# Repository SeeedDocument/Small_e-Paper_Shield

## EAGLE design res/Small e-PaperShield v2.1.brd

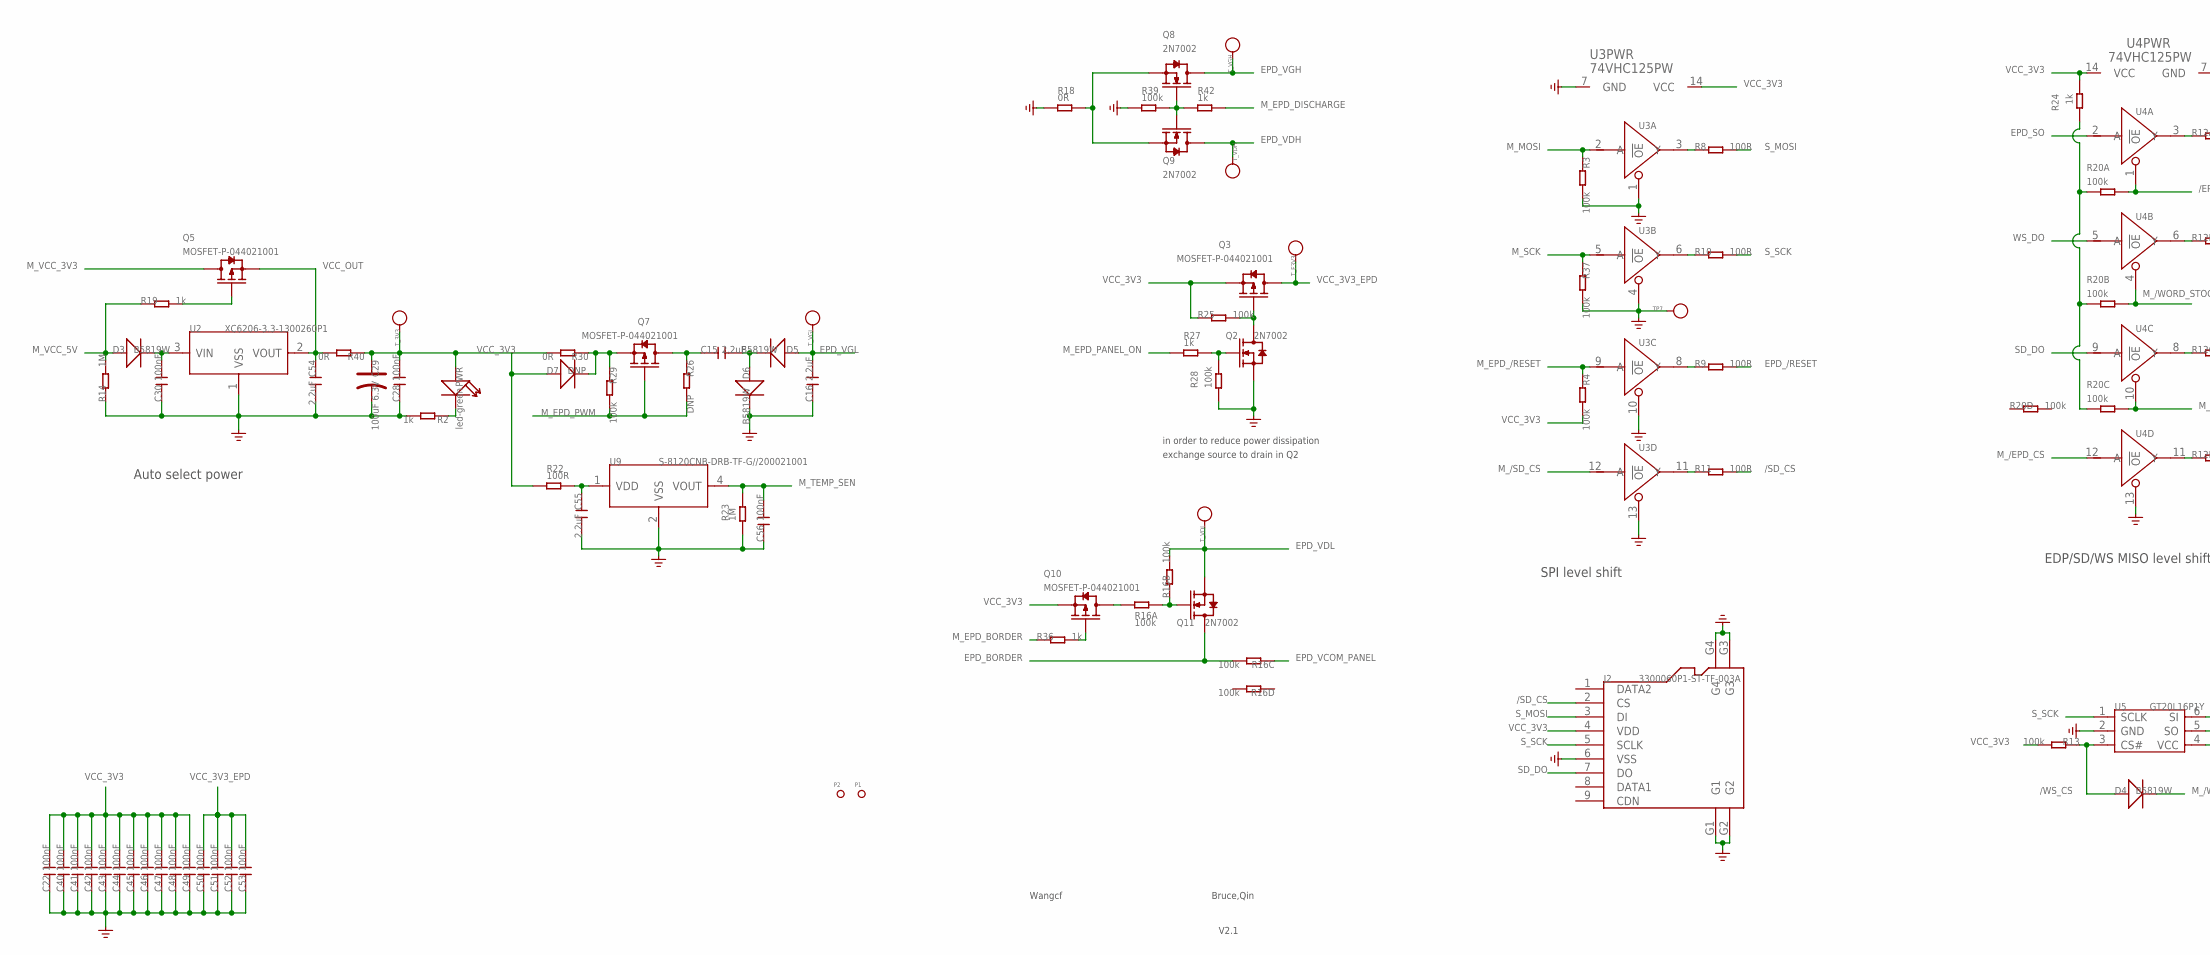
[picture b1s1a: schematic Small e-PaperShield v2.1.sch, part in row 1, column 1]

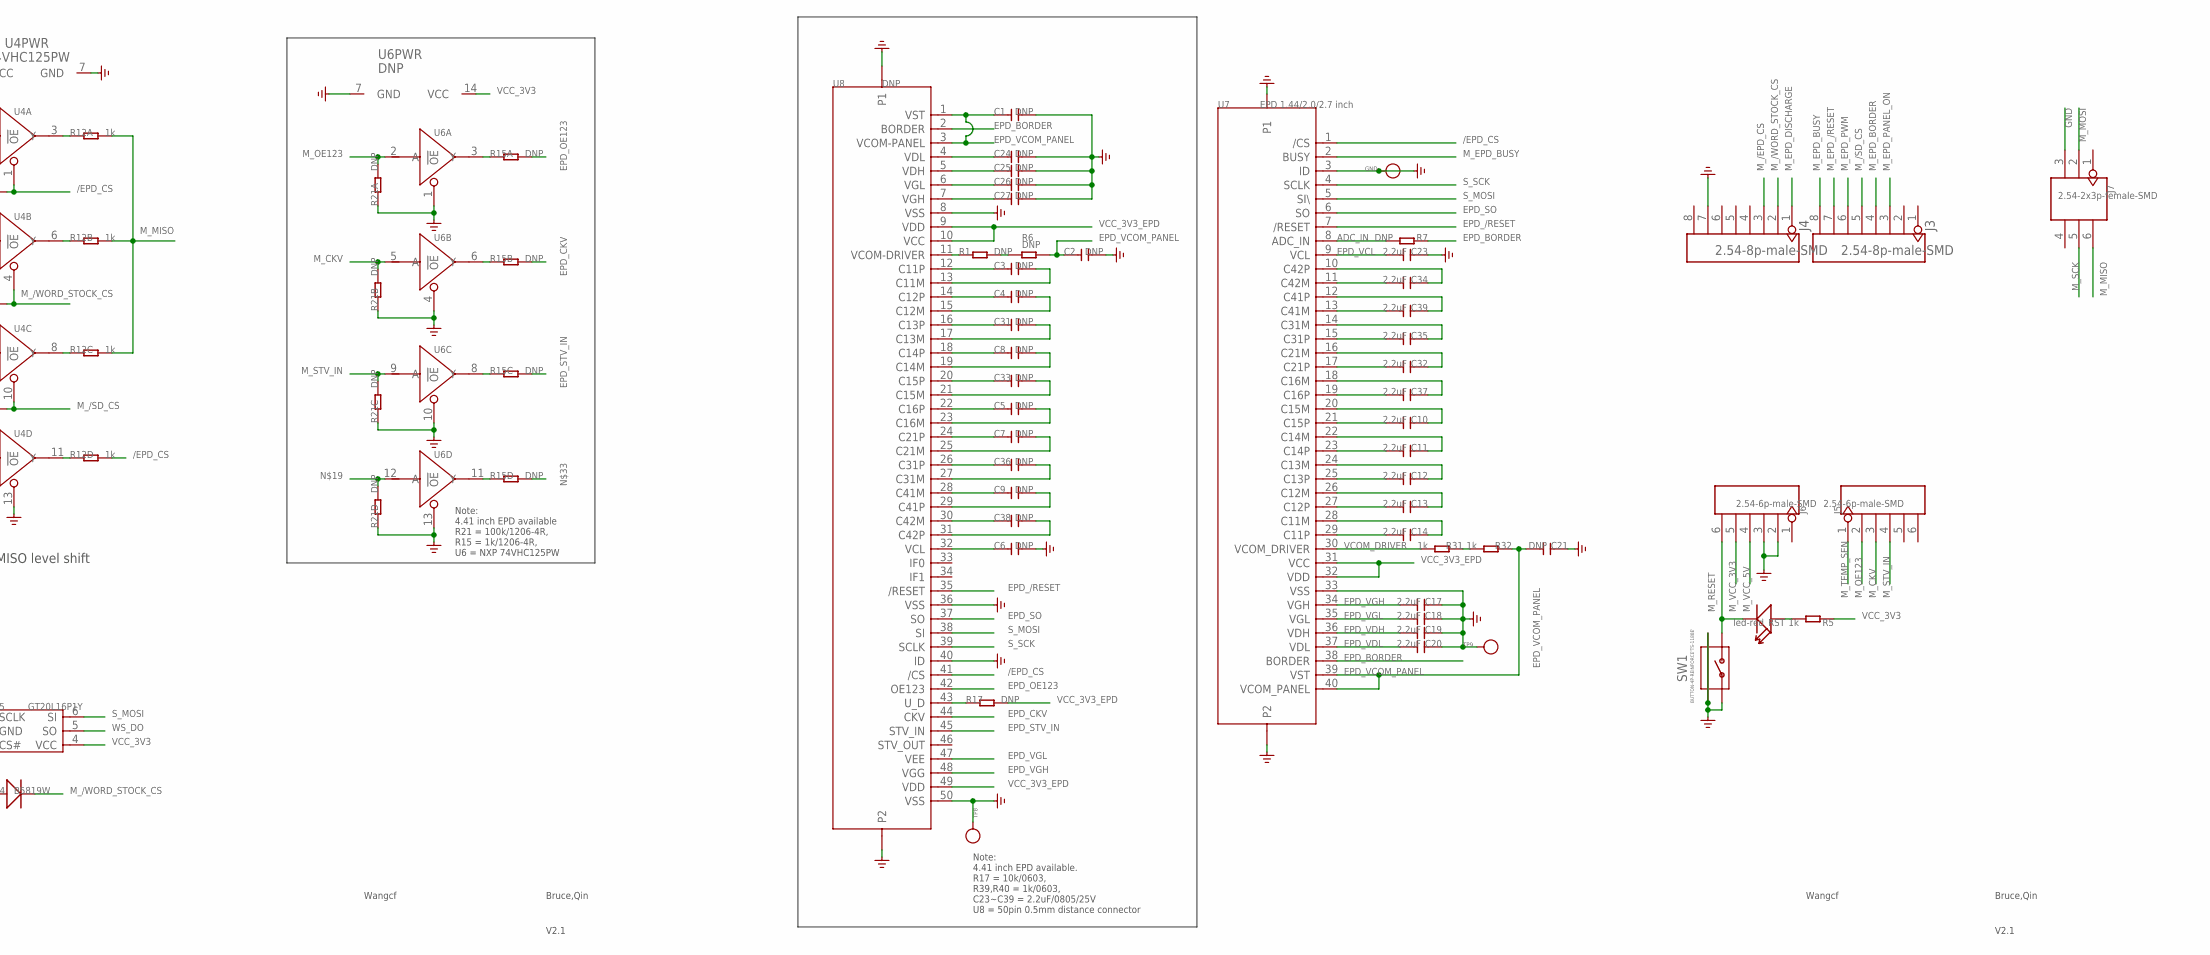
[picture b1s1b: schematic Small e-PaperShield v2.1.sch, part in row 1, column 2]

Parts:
C1, C2, C3, C4, C5, C6, C7, C8, C9, C21, C24, C25, C26, C27, C31, C33, C36, C38: DNP; C0805
C10, C11, C12, C13, C14, C15, C16, C17, C18, C19, C20, C23, C32, C34, C35, C37, C39, C54, C55: 2.2uF; C0805
C22, C28, C30, C40, C41, C42, C43, C44, C45, C46, C47, C48, C49, C50, C51, C52, C53, C56: 100nF; C0603
C29: 100uF 6.3V; AVX-B
D3, D4, D5, D6: B5819W; SOD123
D7: DNP; SOD123
GND: PAD-TEST-POINT'3535'; TP_3535
J2: 3300060P1-ST-TF-003A; 9P-SMD-W/-RING
J3, J4: 2.54-8p-male-SMD; 8P-2.54-SMD
J5, J6: 2.54-6p-male-SMD; 6P-2.54-SMD
J7: 2.54-2x3p-female-SMD; 2X3P-2.54-SMD
P1, P2: PAD-MARK; ROUND-MARK-1.0
PWR: led-green; LED-SIDE-VIEW-0603-RIGHT
Q2, Q8, Q9, Q11: 2N7002; SOT23
Q3, Q5, Q7, Q10: MOSFET-P-044021001; SOT23
R1, R6, R7, R17, R26: DNP; R0603
R2, R5, R19, R24, R27, R31, R32, R36, R42: 1k; R0603
R3, R4, R13, R25, R28, R29, R37, R39: 100k; R0603
R8, R9, R10, R11, R22: 100R; R0603
R12: 1k; 1206-8-3.3X2.4
R14, R23: 1M; R0603
R15, R21: DNP; 1206-8-3.3X2.4
R16, R20: 100k; 1206-8-3.3X2.4
R18, R30, R40: 0R; R0603
RST: led-red; LED-SIDE-VIEW-0603-RIGHT
SW1: BUTTON-4P-REINFORCE'TS-1188E'; 4P-SMD-7X3.5X3.5H
TP7, TP8, TP9: PAD-TEST-POINT'3535'; TP_3535
T_3V3: PAD-TEST-POINT'3535'; TP_3535
T_E3V3: PAD-TEST-POINT'3535'; TP_3535
T_VDH: PAD-TEST-POINT'3535'; TP_3535
T_VDL: PAD-TEST-POINT'3535'; TP_3535
T_VGH: PAD-TEST-POINT'3535'; TP_3535
T_VGL: PAD-TEST-POINT'3535'; TP_3535
U2: XC6206-3.3-1300260P1; SOT23
U3, U4: 74VHC125PW; TSSOP14
U5: GT20L16P1Y; SOT23-6
U6: DNP; TSSOP14
U7: EPD 1.44/2.0/2.7 inch; 40P-0.5
U8: DNP; 50P-0.5
U9: S-8120CNB-DRB-TF-G//200021001; SC-82AB

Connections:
3V3_LOG: R20.1, R20.2 (1), R20.3 (1), R24.2
/EPD_CS: R12.5 (2), R20.8 (2), U4.1 (!OE), U7.1 (/CS), U8.41 (/CS)
/SD_CS: J2.2 (CS), R11.2
/WS_CS: D4.+, R13.1, U5.3 (CS#)
ADC_IN: R7.2, U7.8 (ADC_IN)
EPD_/RESET: R9.2, U7.7 (/RESET), U8.35 (/RESET)
EPD_BORDER: Q11.3 (D), R7.1, R16.6 (2), U7.38 (BORDER), U8.2 (BORDER)
EPD_CKV: R15.7 (2), U8.44 (CKV)
EPD_OE123: R15.8 (2), U8.42 (OE123)
EPD_SO: U4.2 (A), U7.6 (SO), U8.37 (SO)
EPD_STV_IN: R15.6 (2), U8.45 (STV_IN)
EPD_VCL: C23.2, U7.9 (VCL)
EPD_VCOM_PANEL: C1.1, C2.1, C21.2, R6.2, R16.3 (1), R32.1, U7.39 (VST), U7.40 (VCOM_PANEL), U8.1 (VST), U8.3 (VCOM-PANEL)
EPD_VDH: C19.2, C25.1, Q9.3 (D), T_VDH.T, U7.36 (VDH), U8.5 (VDH)
EPD_VDL: C20.2, C24.1, Q11.2 (S), R16.7 (2), T_VDL.T, U7.37 (VDL), U8.4 (VDL)
EPD_VGH: C17.2, C27.1, Q8.3 (D), T_VGH.T, U7.34 (VGH), U8.7 (VGH), U8.48 (VGG)
EPD_VGL: C16.2, C18.2, C26.1, D5.+, T_VGL.T, U7.35 (VGL), U8.6 (VGL), U8.47 (VEE)
GND: C1.2, C2.2, C6.2, C16.1, C17.1, C18.1, C19.1, C20.1, C21.1, C22.1, C23.1, C24.2, C25.2, C26.2, C27.2, C28.1, C29.-, C30.1, C40.1, C41.1, C42.1, C43.1, C44.1, C45.1, C46.1, C47.1, C48.1, C49.1, C50.1, C51.1, C52.1, C53.1, C54.2, C55.2, C56.1, D6.-, GND.T, J2.6 (VSS), J2.G1, J2.G2, J2.G3, J2.G4, J4.7, J6.2, J6.3, J7.3, Q2.2 (S), R2.2, R3.2, R14.1, R18.1, R21.1, R21.2 (1), R21.3 (1), R21.4 (1), R23.1, R28.1, R37.2, R39.1, SW1.1, SW1.S1, SW1.S2, TP7.T, TP8.T, TP9.T, U2.1 (VSS), U3.1 (!OE), U3.4 (!OE), U3.7 (GND), U3.10 (!OE), U3.13 (!OE), U4.7 (GND), U4.13 (!OE), U5.2 (GND), U6.1 (!OE), U6.4 (!OE), U6.7 (GND), U6.10 (!OE), U6.13 (!OE), U7.3 (ID), U7.33 (VSS), U7.P1, U7.P2, U8.8 (VSS), U8.36 (VSS), U8.40 (ID), U8.50 (VSS), U8.P1, U8.P2, U9.2 (VSS)
M_/EPD_CS: J4.3, U4.12 (A)
M_/SD_CS: J3.5, R20.6 (2), U3.12 (A), U4.10 (!OE)
M_/WORD_STOCK_CS: D4.-, J4.2, R20.7 (2), U4.4 (!OE)
M_CKV: J5.3, R21.7 (2), U6.5 (A)
M_EPD_/RESET: J3.7, R4.1, U3.9 (A)
M_EPD_BORDER: J3.4, R36.1
M_EPD_BUSY: J3.8, U7.2 (BUSY)
M_EPD_DISCHARGE: J4.1, R42.2
M_EPD_PANEL_ON: J3.3, R27.1
M_EPD_PWM: J3.6, Q7.1 (G), R26.2, R29.2
M_MISO: J7.6, R12.6 (2), R12.7 (2), R12.8 (2)
M_MOSI: J7.2, R3.1, U3.2 (A)
M_OE123: J5.2, R21.8 (2), U6.2 (A)
M_RESET: J6.6, RST.2 (-), SW1.2
M_SCK: J7.5, R37.1, U3.5 (A)
M_STV_IN: J5.4, R21.6 (2), U6.9 (A)
M_TEMP_SEN: C56.2, J5.1, R23.2, U9.4 (VOUT)
M_VCC_3V3: J6.5, Q5.3 (D)
M_VCC_5V: D3.+, J6.4, R14.2, R19.1
unnamed: PWR.2 (-), R2.1
unnamed: Q5.1 (G), R19.2
unnamed: C15.2, D5.-, D6.+
unnamed: D7.-, Q7.2 (S), R29.1, R30.1
unnamed: Q2.1 (G), R27.2, R28.2
unnamed: R11.1, U3.11 (Y)
unnamed: C30.2, D3.-, U2.3 (VIN)
unnamed: C15.1, Q7.3 (D), R26.1
unnamed: Q8.1 (G), Q9.1 (G), R39.2, R42.1
unnamed: Q2.3 (D), Q3.1 (G), R25.2
unnamed: R31.1, R32.2
unnamed: Q10.3 (D), R16.1
unnamed: Q10.1 (G), R36.2
unnamed: C4.1, U8.14 (C12P)
unnamed: Q8.2 (S), Q9.2 (S), R18.2
unnamed: R21.5 (2), U6.12 (A)
unnamed: R12.1, U4.3 (Y)
unnamed: R12.2 (1), U4.6 (Y)
unnamed: R12.3 (1), U4.8 (Y)
unnamed: R15.1, U6.3 (Y)
unnamed: R15.3 (1), U6.8 (Y)
unnamed: R15.4 (1), U6.11 (Y)
unnamed: R15.2 (1), U6.6 (Y)
unnamed: R12.4 (1), U4.11 (Y)
unnamed: Q11.1 (G), R16.2 (1), R16.8 (2)
unnamed: R1.2, R6.1
unnamed: C34.1, U7.10 (C42P)
unnamed: C34.2, U7.11 (C42M)
unnamed: C39.1, U7.12 (C41P)
unnamed: C39.2, U7.13 (C41M)
unnamed: C4.2, U8.15 (C12M)
unnamed: C3.1, U8.12 (C11P)
unnamed: C31.2, U8.17 (C13M)
unnamed: C31.1, U8.16 (C13P)
unnamed: C8.1, U8.18 (C14P)
unnamed: C8.2, U8.19 (C14M)
unnamed: C33.2, U8.21 (C15M)
unnamed: C33.1, U8.20 (C15P)
unnamed: C5.1, U8.22 (C16P)
unnamed: C5.2, U8.23 (C16M)
unnamed: C7.1, U8.24 (C21P)
unnamed: C7.2, U8.25 (C21M)
unnamed: C36.1, U8.26 (C31P)
unnamed: C36.2, U8.27 (C31M)
unnamed: C9.1, U8.28 (C41M)
unnamed: C9.2, U8.29 (C41P)
unnamed: C38.1, U8.30 (C42M)
unnamed: C38.2, U8.31 (C42P)
unnamed: C6.1, U8.32 (VCL)
unnamed: R1.1, U8.11 (VCOM-DRIVER)
unnamed: R17.1, U8.43 (U_D)
unnamed: R8.1, U3.3 (Y)
unnamed: R10.1, U3.6 (Y)
unnamed: R9.1, U3.8 (Y)
unnamed: C35.1, U7.14 (C31M)
unnamed: C3.2, U8.13 (C11M)
unnamed: C35.2, U7.15 (C31P)
unnamed: R5.2, RST.1 (+)
unnamed: C32.1, U7.16 (C21M)
unnamed: C32.2, U7.17 (C21P)
unnamed: C37.1, U7.18 (C16M)
unnamed: C37.2, U7.19 (C16P)
unnamed: C10.1, U7.20 (C15M)
unnamed: C10.2, U7.21 (C15P)
unnamed: C11.1, U7.22 (C14M)
unnamed: C11.2, U7.23 (C14P)
unnamed: C12.1, U7.24 (C13M)
unnamed: C12.2, U7.25 (C13P)
unnamed: C13.1, U7.26 (C12M)
unnamed: C13.2, U7.27 (C12P)
unnamed: C14.1, U7.28 (C11M)
unnamed: C14.2, U7.29 (C11P)
SD_DO: J2.7 (DO), U4.9 (A)
S_MOSI: J2.3 (DI), R8.2, U5.6 (SI), U7.5 (SI\), U8.38 (SI)
S_SCK: J2.5 (SCLK), R10.2, U5.1 (SCLK), U7.4 (SCLK), U8.39 (SCLK)
VCC_3V3: C22.2, C28.2, C29.+, C40.2, C41.2, C42.2, C43.2, C44.2, C45.2, C46.2, C47.2, C48.2, C49.2, D7.+, J2.4 (VDD), PWR.1 (+), Q3.2 (S), Q10.2 (S), R4.2, R5.1, R13.2, R22.1, R24.1, R25.1, R30.2, R40.1, T_3V3.T, U3.14 (VCC), U4.14 (VCC), U5.4 (VCC), U6.14 (VCC)
VCC_3V3_EPD: C50.2, C51.2, C52.2, C53.2, Q3.3 (D), R17.2, T_E3V3.T, U7.31 (VCC), U7.32 (VDD), U8.9 (VDD), U8.10 (VCC), U8.49 (VDD)
VCC_OUT: C54.1, Q5.2 (S), R40.2, U2.2 (VOUT)
VCOM_DRIVER: R31.2, U7.30 (VCOM_DRIVER)
VDD: C55.1, R22.2, U9.1 (VDD)
WS_DO: U4.5 (A), U5.5 (SO)

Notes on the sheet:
EDP/SD/WS MISO level shift
SPI level shift
Auto select power
Bruce,Qin
V2.1
Note: 4.41 inch EPD available. R17 = 10k/0603, R39,R40 = 1k/0603, C23~C39 = 2.2uF/0805/25V U8 = 50pin 0.5mm distance connector
Note: 4.41 inch EPD available R21 = 100k/1206-4R, R15 = 1k/1206-4R, U6 = NXP 74VHC125PW
Wangcf
in order to reduce power dissipation
exchange source to drain in Q2

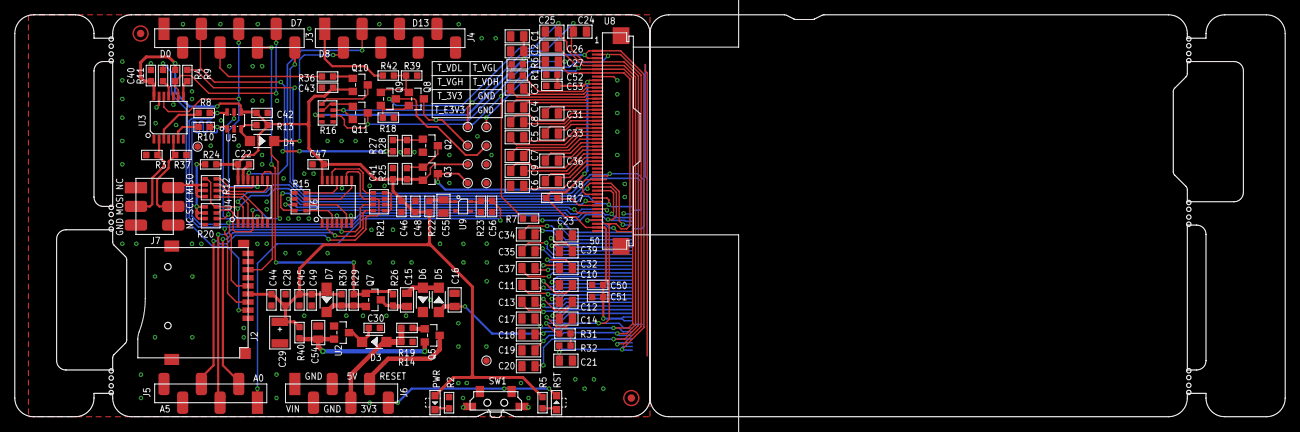
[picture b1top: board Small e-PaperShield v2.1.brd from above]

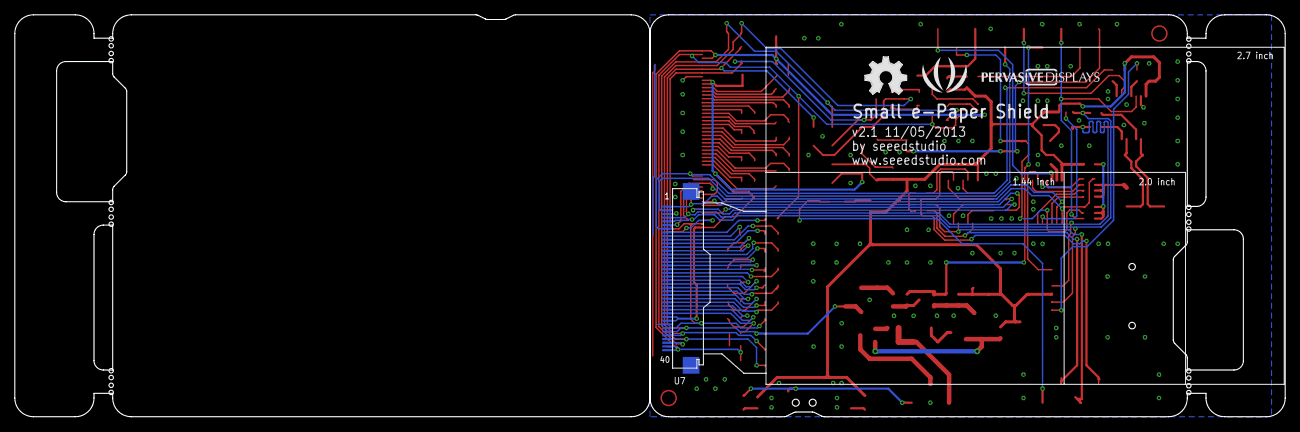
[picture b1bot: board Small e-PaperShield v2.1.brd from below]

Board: 2 copper layers, 172.6 x 54.6 mm, 137 parts (3 on the bottom side), 118 nets.

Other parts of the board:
U$20: LOGO_SILK
U$47: OSHW_FILLX200_NOTEXT

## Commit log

2017-06-04 upgrade
